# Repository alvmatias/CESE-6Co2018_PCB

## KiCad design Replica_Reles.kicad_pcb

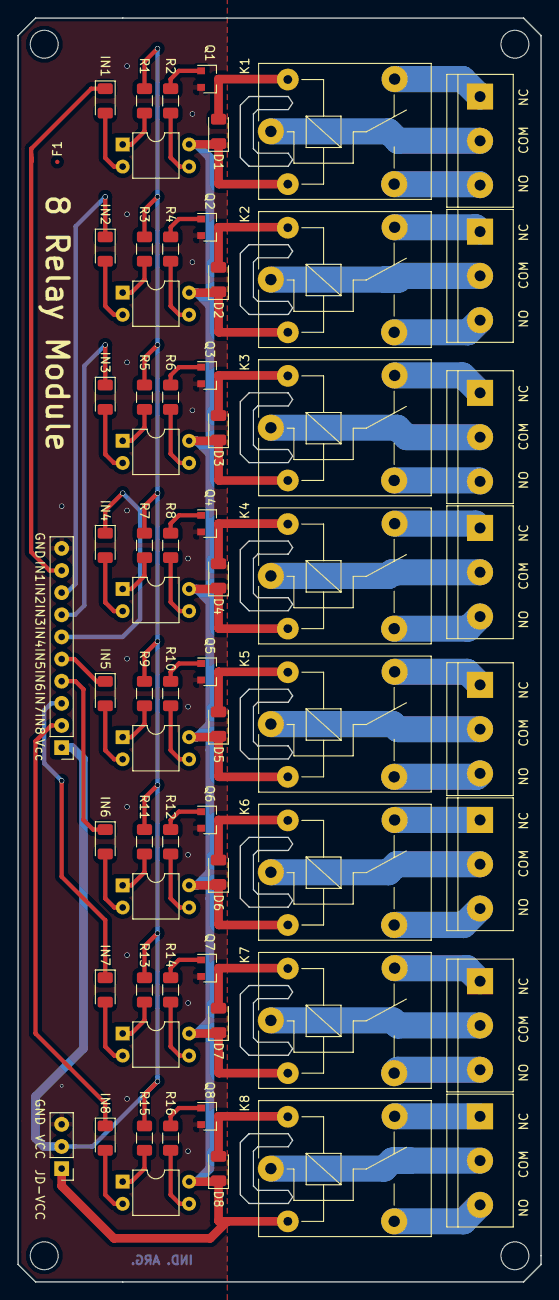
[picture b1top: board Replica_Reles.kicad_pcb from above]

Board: 2 copper layers, 60.0 x 145.0 mm, 71 parts (0 on the bottom side), 75 nets.

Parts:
D1, D2, D3, D4, D5, D6, D7, D8: 1N4148; D_1206_3216Metric
F1: Fiducial; Fiducial_0.5mm_Dia_1mm_Outer
IN1, IN2, IN3, IN4, IN5, IN6, IN7, IN8: LED ROJO SMD; LED_1206_3216Metric
J1, J2, J4, J5, J6, J7, J8, J9: Bornera; TerminalBlock_bornier-3_P5.08mm
J3: Tira de Pines Macho; PinHeader_1x10_P2.54mm_Vertical
J10: Tira de Pines Macho; PinHeader_1x03_P2.54mm_Vertical
K1, K2, K3, K4, K5, K6, K7, K8: SONGLE_SRD_Form_C; Relay_SPDT_SONGLE_SRD_Series_Form_C
MH1, MH2, MH3, MH4: MountingHole; MountingHole_3.2mm_M3_ISO14580
Q1, Q2, Q3, Q4, Q5, Q6, Q7, Q8: S8050; SOT-23
R1, R3, R5, R7, R9, R11, R13, R15: 1000; R_1206_3216Metric
R2, R4, R6, R8, R10, R12, R14, R16: 510; R_1206_3216Metric
U1, U2, U3, U4, U5, U6, U7, U8: PC817; DIP-4_W7.62mm

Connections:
+5V: J3.1, J10.2, R1.1, R3.1, R5.1, R7.1, R9.1, R11.1, R13.1, R15.1
/IN1: IN1.1, J3.9
/IN2: IN2.1, J3.8
/IN3: IN3.1, J3.7
/IN4: IN4.1, J3.6
/IN5: IN5.1, J3.5
/IN6: IN6.1, J3.4
/IN7: IN7.1, J3.3
/IN8: IN8.1, J3.2
/JD-VCC: D1.1, D2.1, D3.1, D4.1, D5.1, D6.1, D7.1, D8.1, J10.1, K1.5, K2.5, K3.5, K4.5, K5.5, K6.5, K7.5, K8.5, U1.4, U2.4, U3.4, U4.4, U5.4, U6.4, U7.4, U8.4
GND: J3.10, J10.3, Q1.2, Q2.2, Q3.2, Q4.2, Q5.2, Q6.2, Q7.2, Q8.2
unnamed: D1.2, K1.2, Q1.3
unnamed: D2.2, K2.2, Q2.3
unnamed: D3.2, K3.2, Q3.3
unnamed: D4.2, K4.2, Q4.3
unnamed: D5.2, K5.2, Q5.3
unnamed: D6.2, K6.2, Q6.3
unnamed: D7.2, K7.2, Q7.3
unnamed: D8.2, K8.2, Q8.3
unnamed: IN1.2, U1.2
unnamed: IN2.2, U2.2
unnamed: IN3.2, U3.2
unnamed: IN4.2, U4.2
unnamed: IN5.2, U5.2
unnamed: IN6.2, U6.2
unnamed: IN7.2, U7.2
unnamed: IN8.2, U8.2
unnamed: J1.1, K1.4
unnamed: J1.2, K1.1
unnamed: J1.3, K1.3
unnamed: J2.1, K2.4
unnamed: J2.2, K2.1
unnamed: J2.3, K2.3
unnamed: J4.1, K3.4
unnamed: J4.2, K3.1
unnamed: J4.3, K3.3
unnamed: J5.1, K4.4
unnamed: J5.2, K4.1
unnamed: J5.3, K4.3
unnamed: J6.1, K5.4
unnamed: J6.2, K5.1
unnamed: J6.3, K5.3
unnamed: J7.1, K6.4
unnamed: J7.2, K6.1
unnamed: J7.3, K6.3
unnamed: J8.1, K7.4
unnamed: J8.2, K7.1
unnamed: J8.3, K7.3
unnamed: J9.1, K8.4
unnamed: J9.2, K8.1
unnamed: J9.3, K8.3
unnamed: Q1.1, R2.1
unnamed: Q2.1, R4.1
unnamed: Q3.1, R6.1
unnamed: Q4.1, R8.1
unnamed: Q5.1, R10.1
unnamed: Q6.1, R12.1
unnamed: Q7.1, R14.1
unnamed: Q8.1, R16.1
unnamed: R1.2, U1.1
unnamed: R2.2, U1.3
unnamed: R3.2, U2.1
unnamed: R4.2, U2.3
unnamed: R5.2, U3.1
unnamed: R6.2, U3.3
unnamed: R7.2, U4.1
unnamed: R8.2, U4.3
unnamed: R9.2, U5.1
unnamed: R10.2, U5.3
unnamed: R11.2, U6.1
unnamed: R12.2, U6.3
unnamed: R13.2, U7.1
unnamed: R14.2, U7.3
unnamed: R15.2, U8.1
unnamed: R16.2, U8.3

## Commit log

2018-09-08 Creacion Repositorio
2018-09-21 Revision 1.0: Diseño de Esquematico
2018-09-22 Inicio PCB: Posicionamiento de Componentes
2018-09-28 Agregado de documentacion
2018-09-28 Arreglo de modelos 3D
2018-09-29 Mas documentacion
2018-10-01 Cambios en posicionamiento, ruteo y mas documentacion
2018-10-06 Arreglos menores y agregado de documentacion
2018-10-13 Agregado fiduciales, texto en capa de cobre y arreglo de errores
2018-10-19 Arreglos de revision - Problema persistente: No es posible visualizar huella propia de los reles
2018-10-19 Error footprint propio solucionado
2018-10-31 Arreglos luego de la revision del profesor
2018-11-02 Licencia
